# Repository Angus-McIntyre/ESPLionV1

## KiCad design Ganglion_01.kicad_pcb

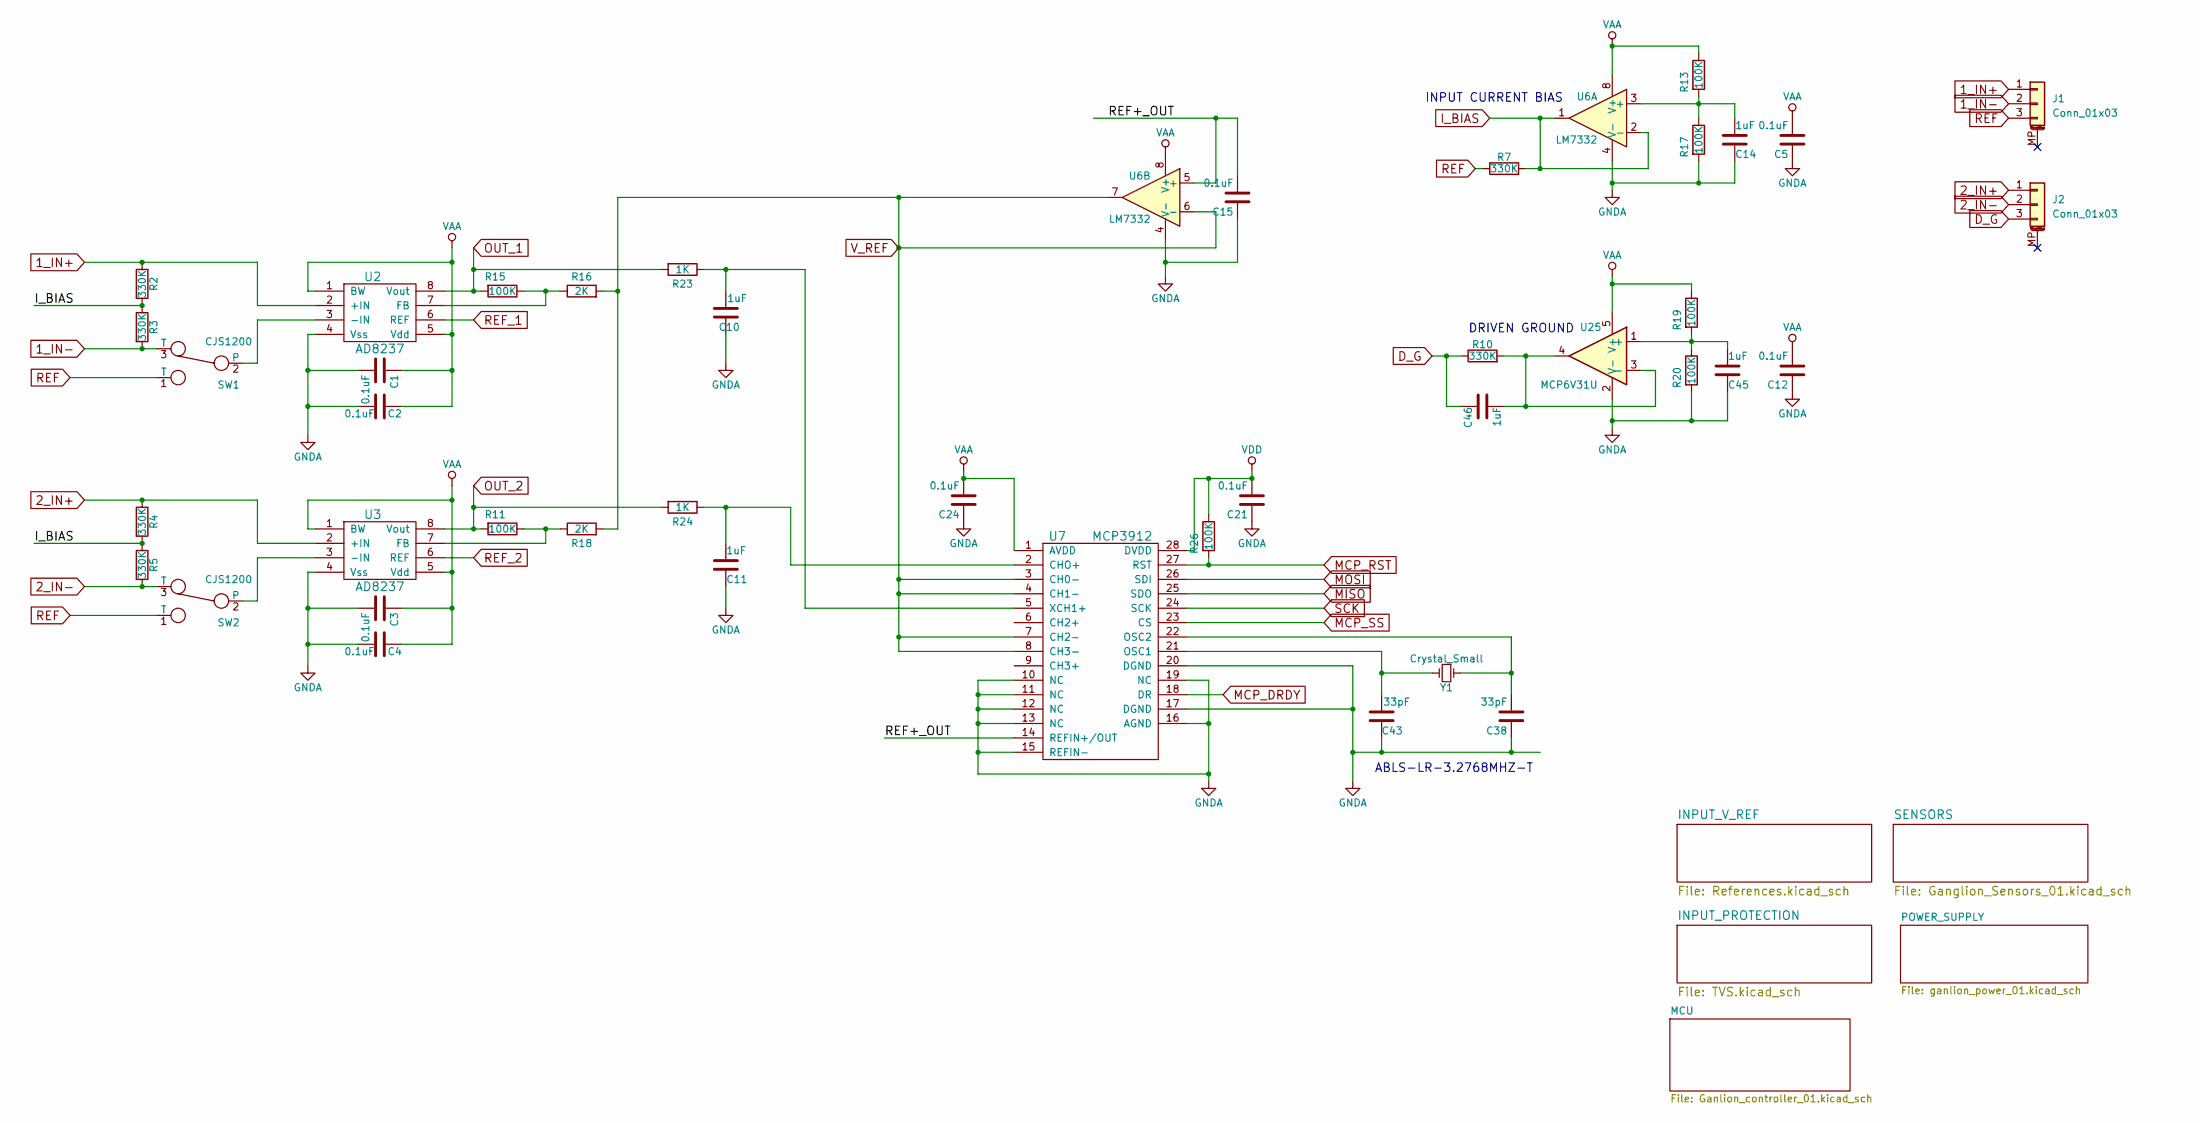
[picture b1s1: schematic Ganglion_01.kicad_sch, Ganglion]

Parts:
C1, C2, C3, C4, C5, C12, C15, C21, C24: 0.1uF; C_0402_1005Metric; MPN GRM155R71C104KA88J
C10, C11, C14, C45, C46: 1uF; C_0603_1608Metric; MPN CC0603KRX7R7BB105
C38, C43: 33pF; C_0603_1608Metric; MPN CL10C330JB8NNNC
J1, J2: Conn_01x03; JST_PH_S3B-PH-SM4-TB_1x03-1MP_P2.00mm_Horizontal; MPN S3B-PH-SM4-TB
R2, R3, R4, R5, R7, R10: 330K; R_0402_1005Metric; MPN ERJ-2RKF3303X
R11, R13, R15, R17, R19, R20, R26: 100K; R_0402_1005Metric; MPN ERJ-2RKF1003X
R16, R18: 2K; R_0402_1005Metric; MPN ERJ-2RKF2001X
R23, R24: 1K; R_0402_1005Metric; MPN ERJ-2RKF1001X
SW1, SW2: CJS1200; CJS-1200TA; MPN CJS-1200TA
U2, U3: AD8237; MSOP-8_3x3mm_P0.65mm; MPN AD8237ARMZ
U6: LM7332; MSOP-8_3x3mm_P0.65mm; MPN LM7332MMX/NOPB
U7: MCP3912; SSOP-28_5.3x10.2mm_P0.65mm; MPN MCP3912A1-E/SS
U25: MCP6V31U; SOT-353_SC-70-5; MPN MCP6V31UT-E/LT
Y1: Crystal_Small; Crystal_SMD_HC49-SD; MPN ABLS-LR-3.2768MHZ-T

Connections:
1_IN+: J1.1, R2.1, U2.2 (+IN); also elsewhere on the board
1_IN-: J1.2, R3.2, SW1.3 (T); also elsewhere on the board
2_IN+: J2.1, R4.1, U3.2 (+IN); also elsewhere on the board
2_IN-: J2.2, R5.2, SW2.3 (T); also elsewhere on the board
/REF+_OUT: C15.2, U6.5 (+), U7.14 (REFIN+/OUT)
D_G: C46.2, J2.3, R10.1; also elsewhere on the board
GNDA: C1.2, C2.2, C3.2, C4.2, C5.1, C10.1, C11.2, C12.1, C14.2, C15.1, C21.1, C24.1, C38.1, C43.1, C45.2, R17.2, R20.2, U2.4 (Vss), U3.4 (Vss), U6.4 (V-), U7.10 (NC), U7.11 (NC), U7.12 (NC), U7.13 (NC), U7.15 (REFIN-), U7.16 (AGND), U7.17 (DGND), U7.19 (NC), U7.20 (DGND), U25.2 (V-); also elsewhere on the board
I_BIAS: R2.2, R3.1, R4.2, R5.1, R7.2, U6.1, U6.2 (-)
MCP_DRDY: U7.18 (DR); also elsewhere on the board
MCP_RST: R26.2, U7.27 (RST); also elsewhere on the board
MCP_SS: U7.23 (CS); also elsewhere on the board
MISO: U7.25 (SDO); also elsewhere on the board
MOSI: U7.26 (SDI); also elsewhere on the board
unnamed: SW1.2, U2.3 (-IN)
unnamed: SW2.2, U3.3 (-IN)
unnamed: R15.1, R16.1, U2.7 (FB)
unnamed: R11.1, R18.1, U3.7 (FB)
unnamed: C14.1, R13.2, R17.1, U6.3 (+)
unnamed: C11.1, R24.1, U7.2 (CHO+)
unnamed: C43.2, U7.21 (OSC1), Y1.2
unnamed: C38.2, U7.22 (OSC2), Y1.1
unnamed: C10.2, R23.1, U7.5 (XCH1+)
unnamed: C45.1, R19.2, R20.1, U25.1 (+)
unnamed: C46.1, R10.2, U25.3 (-), U25.4
OUT_1: R15.2, R23.2, U2.8 (Vout); also elsewhere on the board
OUT_2: R11.2, R24.2, U3.8 (Vout); also elsewhere on the board
REF: J1.3, R7.1, SW1.1 (T), SW2.1 (T); also elsewhere on the board
REF_1: U2.6 (REF); also elsewhere on the board
REF_2: U3.6 (REF); also elsewhere on the board
SCK: U7.24 (SCK); also elsewhere on the board
VAA: C1.1, C2.1, C3.1, C4.1, C5.2, C12.2, C24.2, R13.1, R19.1, U2.1 (BW), U2.5 (Vdd), U3.1 (BW), U3.5 (Vdd), U6.8 (V+), U7.1 (AVDD), U25.5 (V+); also elsewhere on the board
VDD: C21.2, R26.1, U7.28 (DVDD); also elsewhere on the board
V_REF: R16.2, R18.2, U6.6 (-), U6.7, U7.3 (CH0-), U7.4 (CH1-), U7.7 (CH2-), U7.8 (CH3-); also elsewhere on the board

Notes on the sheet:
INPUT CURRENT BIAS
ABLS-LR-3.2768MHZ-T
DRIVEN GROUND

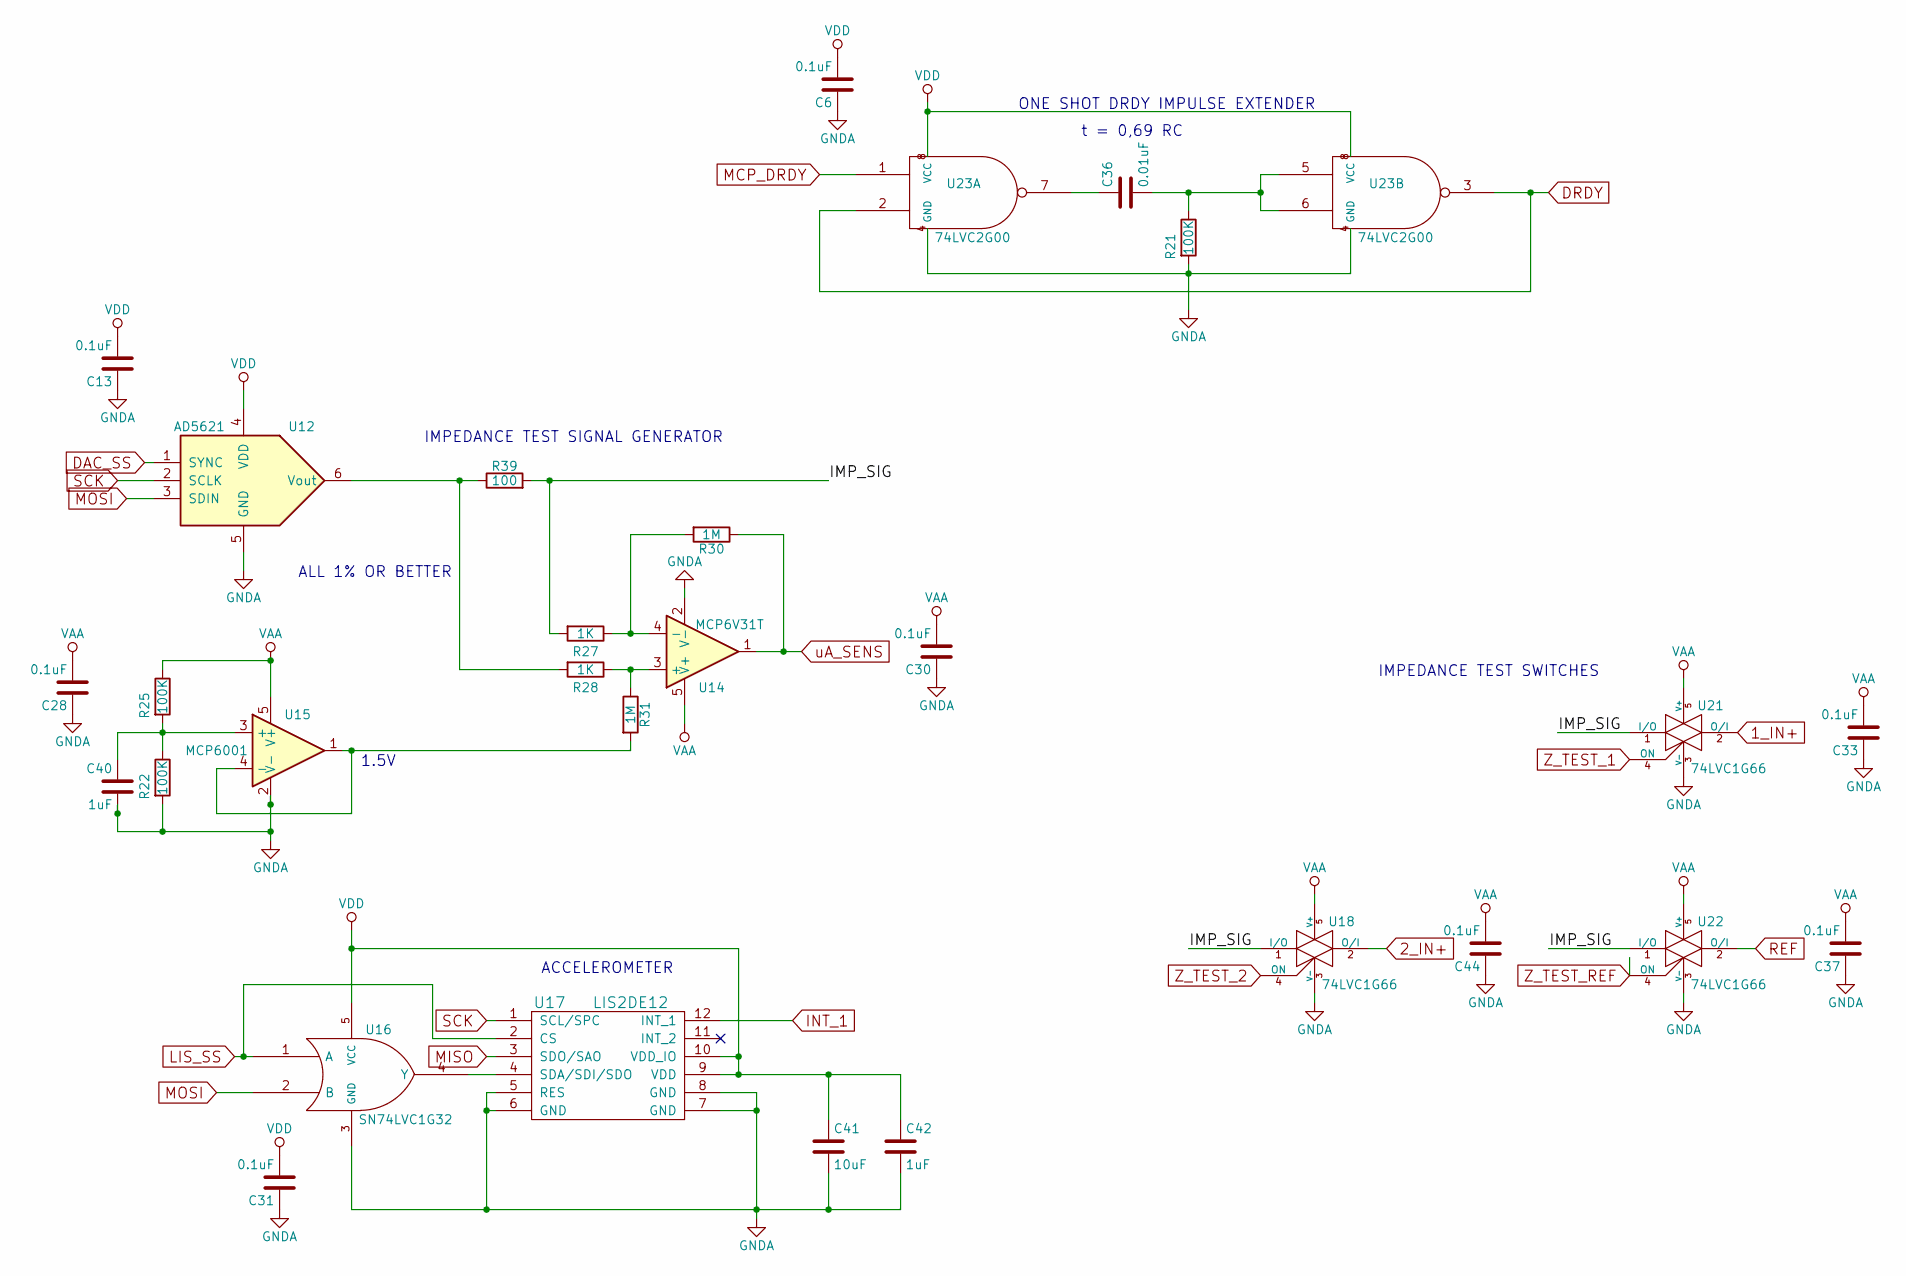
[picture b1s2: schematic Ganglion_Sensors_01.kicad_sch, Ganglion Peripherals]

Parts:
C6, C13, C28, C30, C31, C33, C37, C44: 0.1uF; C_0402_1005Metric; MPN GRM155R71C104KA88J
C36: 0.01uF; C_0603_1608Metric; MPN GCM188R72A103KA37D
C40, C42: 1uF; C_0603_1608Metric; MPN CC0603KRX7R7BB105
C41: 10uF; C_0603_1608Metric; MPN GRM188R60J106KE47D
R21, R22, R25: 100K; R_0402_1005Metric; MPN ERJ-2RKF1003X
R27, R28: 1K; R_0402_1005Metric; MPN ERJ-2RKF1001X
R30, R31: 1M; R_0402_1005Metric; MPN ERJ-2RKF1004X
R39: 100; R_0603_1608Metric; MPN ERA-3AEB101V
U12: AD5621; SOT-363_SC-70-6; MPN AD5621AKSZ-REEL7
U14: MCP6V31T; SOT-23-5; MPN MCP6V31T-E/OT
U15: MCP6001; SOT-353_SC-70-5; MPN MCP6001T-I/LT
U16: SN74LVC1G32; SOT-353_SC-70-5; MPN SN74LVC1G32DCKR
U17: LIS2DE12; LIS2DH12; MPN LIS2DE12TR
U18, U21, U22: 74LVC1G66; SOT-353_SC-70-5; MPN 74LVC1G66GW,125
U23: 74LVC2G00; VSSOP-8; MPN SN74LVC2G00DCUR

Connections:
1_IN+: U21.2 (O/I); also elsewhere on the board
2_IN+: U18.2 (O/I); also elsewhere on the board
/SENSORS/IMP_SIG: R27.2, R39.2, U18.1 (I/O), U21.1 (I/O), U22.1 (I/O)
DAC_SS: U12.1 (SYNC); also elsewhere on the board
DRDY: U23.2, U23.3; also elsewhere on the board
GNDA: C6.1, C13.1, C28.1, C30.1, C31.1, C33.1, C37.1, C40.2, C41.2, C42.2, C44.1, R21.2, R22.2, U12.5 (GND), U14.2 (V-), U15.2 (V-), U16.3 (GND), U17.5 (RES), U17.6 (GND), U17.7 (GND), U17.8 (GND), U18.3 (V-), U21.3 (V-), U22.3 (V-), U23.4 (GND); also elsewhere on the board
INT_1: U17.12 (INT_1); also elsewhere on the board
LIS_SS: U16.1 (A), U17.2 (CS); also elsewhere on the board
MCP_DRDY: U23.1; also elsewhere on the board
MISO: U17.3 (SDO/SAO); also elsewhere on the board
MOSI: U12.3 (SDIN), U16.2 (B); also elsewhere on the board
unnamed: C36.1, U23.7
unnamed: C36.2, R21.1, U23.5, U23.6
unnamed: R28.2, R39.1, U12.6 (Vout)
unnamed: R28.1, R31.1, U14.3 (+)
unnamed: R27.1, R30.2, U14.4 (-)
unnamed: C40.1, R22.1, R25.2, U15.3 (+)
unnamed: R31.2, U15.1, U15.4 (-)
unnamed: U16.4 (Y), U17.4 (SDA/SDI/SDO)
REF: U22.2 (O/I); also elsewhere on the board
SCK: U12.2 (SCLK), U17.1 (SCL/SPC); also elsewhere on the board
VAA: C28.2, C30.2, C33.2, C37.2, C44.2, R25.1, U14.5 (V+), U15.5 (V+), U18.5 (V+), U21.5 (V+), U22.5 (V+); also elsewhere on the board
VDD: C6.2, C13.2, C31.2, C41.1, C42.1, U12.4 (VDD), U16.5 (VCC), U17.9 (VDD), U17.10 (VDD_IO), U23.8 (VCC); also elsewhere on the board
Z_TEST_1: U21.4 (ON); also elsewhere on the board
Z_TEST_2: U18.4 (ON); also elsewhere on the board
Z_TEST_REF: U22.4 (ON); also elsewhere on the board
uA_SENS: R30.1, U14.1; also elsewhere on the board

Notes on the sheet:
ONE SHOT DRDY IMPULSE EXTENDER
t = 0,69 RC
1.5V
ACCELEROMETER
IMPEDANCE TEST SIGNAL GENERATOR
ALL 1% OR BETTER
IMPEDANCE TEST SWITCHES

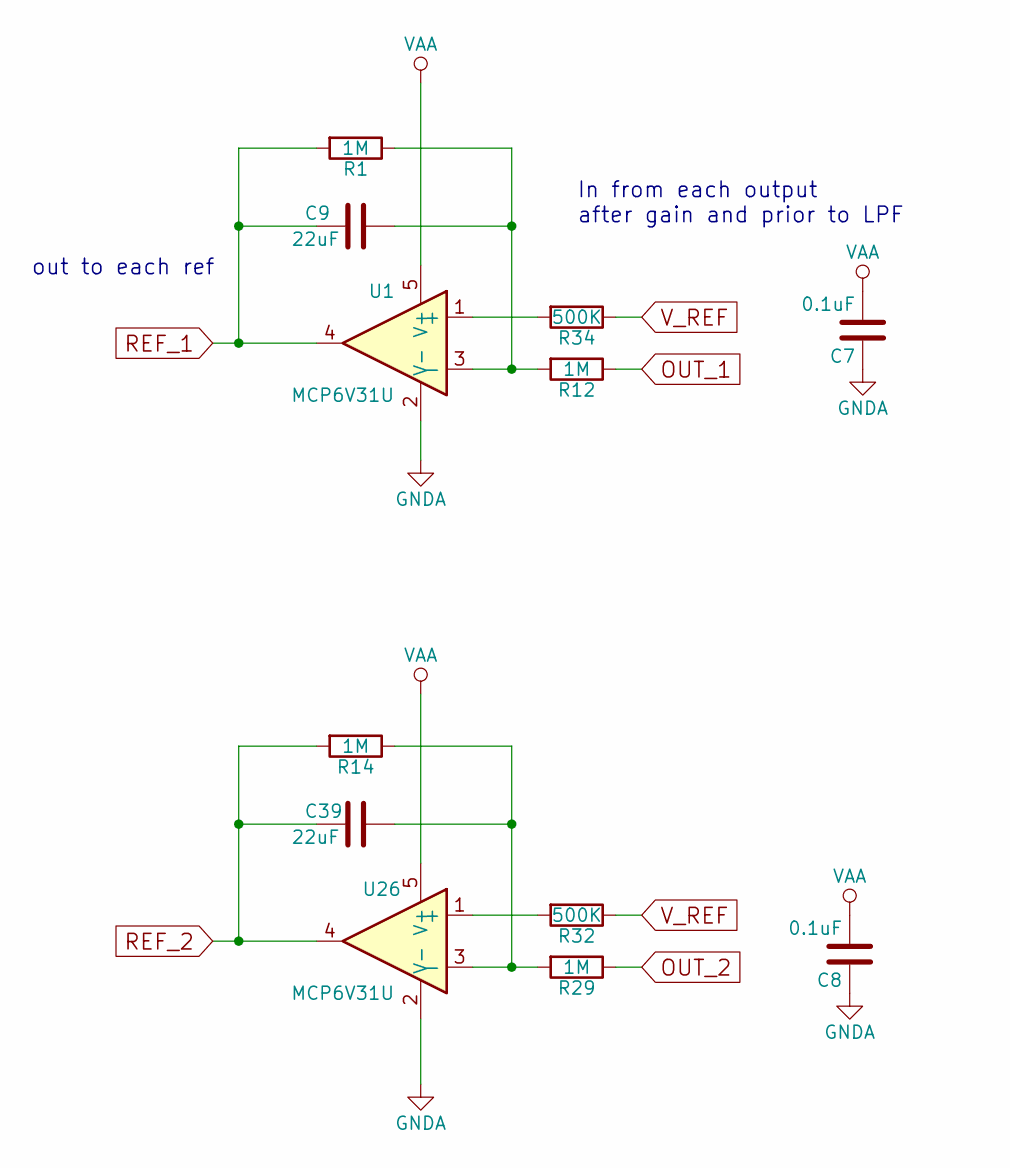
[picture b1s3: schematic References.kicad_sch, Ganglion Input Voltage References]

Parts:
C7, C8: 0.1uF; C_0402_1005Metric; MPN GRM155R71C104KA88J
C9, C39: 22uF; C_0603_1608Metric; MPN GRM188R60J226MEA0D
R1, R12, R14, R29: 1M; R_0402_1005Metric; MPN ERJ-2RKF1004X
R32, R34: 500K; R_0402_1005Metric; MPN ERJ-2RKF4993X
U1, U26: MCP6V31U; SOT-353_SC-70-5; MPN MCP6V31UT-E/LT

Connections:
GNDA: C7.1, C8.1, U1.2 (V-), U26.2 (V-); also elsewhere on the board
unnamed: R34.2, U1.1 (+)
unnamed: C9.1, R1.1, R12.2, U1.3 (-)
unnamed: R32.2, U26.1 (+)
unnamed: C39.1, R14.1, R29.2, U26.3 (-)
OUT_1: R12.1; also elsewhere on the board
OUT_2: R29.1; also elsewhere on the board
REF_1: C9.2, R1.2, U1.4; also elsewhere on the board
REF_2: C39.2, R14.2, U26.4; also elsewhere on the board
VAA: C7.2, C8.2, U1.5 (V+), U26.5 (V+); also elsewhere on the board
V_REF: R32.1, R34.1; also elsewhere on the board

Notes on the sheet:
In from each output after gain and prior to LPF
out to each ref

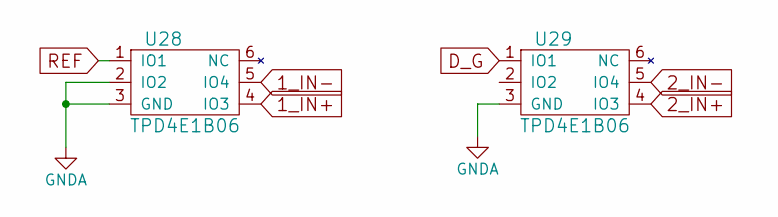
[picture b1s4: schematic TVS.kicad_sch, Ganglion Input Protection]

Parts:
U28, U29: TPD4E1B06; SOT-363_SC-70-6; MPN TPD4E1B06DCKR

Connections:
1_IN+: U28.4 (IO3); also elsewhere on the board
1_IN-: U28.5 (IO4); also elsewhere on the board
2_IN+: U29.4 (IO3); also elsewhere on the board
2_IN-: U29.5 (IO4); also elsewhere on the board
D_G: U29.1 (IO1); also elsewhere on the board
GNDA: U28.2 (IO2), U28.3 (GND), U29.3 (GND); also elsewhere on the board
REF: U28.1 (IO1); also elsewhere on the board

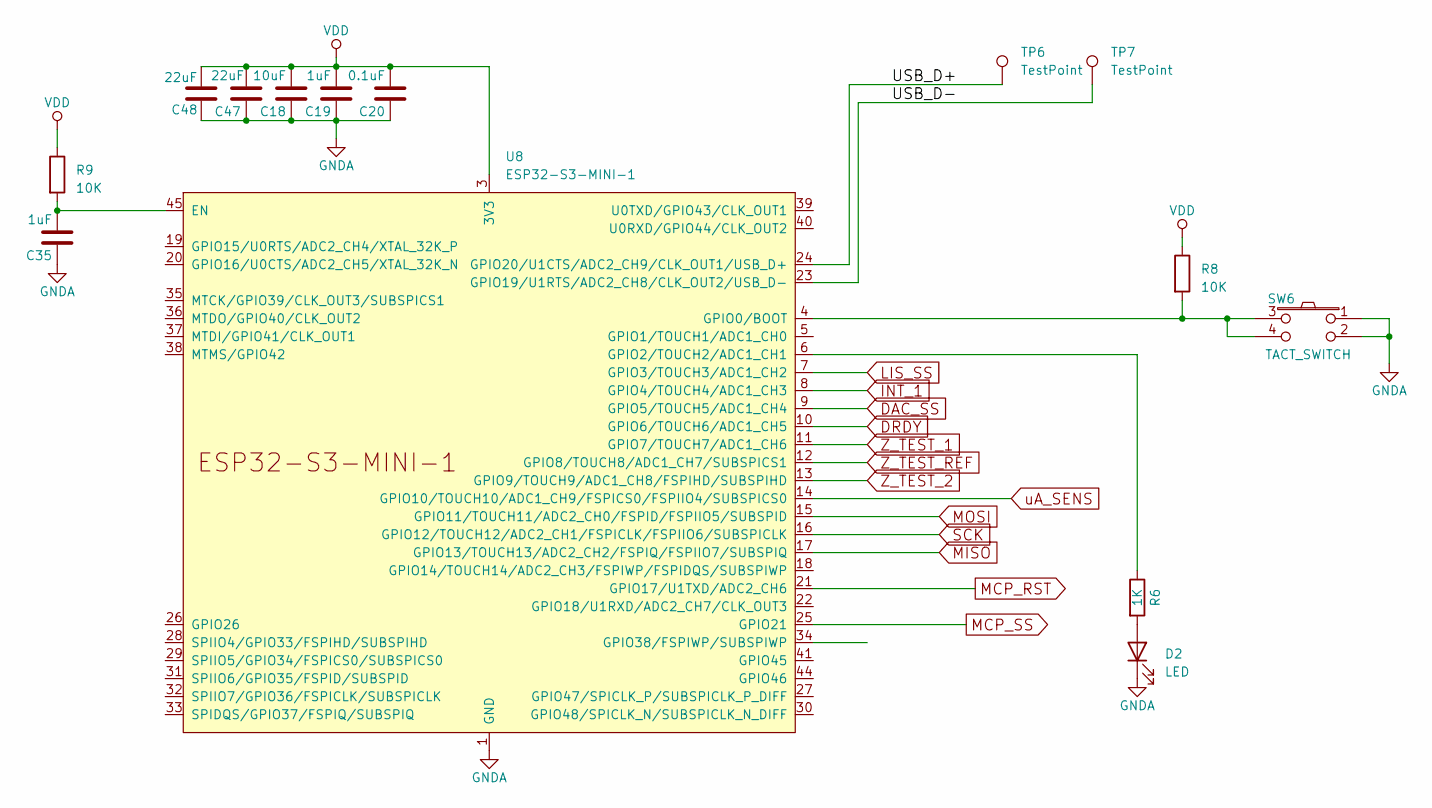
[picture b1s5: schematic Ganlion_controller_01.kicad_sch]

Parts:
C18: 10uF; C_0603_1608Metric; MPN GRM188R60J106KE47D
C19, C35: 1uF; C_0603_1608Metric; MPN CC0603KRX7R7BB105
C20: 0.1uF; C_0402_1005Metric; MPN GRM155R71C104KA88J
C47, C48: 22uF; C_0603_1608Metric; MPN GRM188R60J226MEA0D
D2: LED; LED_0603_1608Metric_Pad1.05x0.95mm_HandSolder; MPN 150060VS75003
R6: 1K; R_0402_1005Metric; MPN ERJ-2RKF1001X
R8, R9: 10K; R_0402_1005Metric; MPN ERJ-2RKF1002X
SW6: TACT_SWITCH; PTS810; MPN PTS810 SJK 250 SMTR LFS
TP6, TP7: TestPoint; TestPoint_Pad_D1.5mm
U8: ESP32-S3-MINI-1; MPN ESP32-S3-MINI-1-N8

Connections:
/MCU/USB_D+: TP6.1, U8.24 (GPIO20/U1CTS/ADC2_CH9/CLK_OUT1/USB_D+)
/MCU/USB_D-: TP7.1, U8.23 (GPIO19/U1RTS/ADC2_CH8/CLK_OUT2/USB_D-)
DAC_SS: U8.9 (GPIO5/TOUCH5/ADC1_CH4); also elsewhere on the board
DRDY: U8.10 (GPIO6/TOUCH6/ADC1_CH5); also elsewhere on the board
GNDA: C18.1, C19.1, C20.1, C35.1, C47.2, C48.2, D2.1 (K), SW6.1, SW6.2, U8.1 (GND), U8.2 (GND), U8.42 (GND), U8.43 (GND), U8.46 (GND), U8.47 (GND), U8.48 (GND), U8.49 (GND), U8.50 (GND), U8.51 (GND), U8.52 (GND), U8.53 (GND), U8.54 (GND), U8.55 (GND), U8.56 (GND), U8.57 (GND), U8.58 (GND), U8.59 (GND), U8.60 (GND), U8.61 (GND), U8.62 (GND), U8.63 (GND), U8.64 (GND), U8.65 (GND); also elsewhere on the board
INT_1: U8.8 (GPIO4/TOUCH4/ADC1_CH3); also elsewhere on the board
LIS_SS: U8.7 (GPIO3/TOUCH3/ADC1_CH2); also elsewhere on the board
MCP_RST: U8.21 (GPIO17/U1TXD/ADC2_CH6); also elsewhere on the board
MCP_SS: U8.25 (GPIO21); also elsewhere on the board
MISO: U8.17 (GPIO13/TOUCH13/ADC2_CH2/FSPIQ/FSPIIO7/S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); also elsewhere on the board
MOSI: U8.15 (GPIO11/TOUCH11/ADC2_CH0/FSPID/FSPIIO5/S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); also elsewhere on the board
unnamed: D2.2 (A), R6.2
unnamed: C35.2, R9.2, U8.45 (EN)
unnamed: R8.2, SW6.3, SW6.4, U8.4 (GPIO0/BOOT)
unnamed: R6.1, U8.6 (GPIO2/TOUCH2/ADC1_CH1)
SCK: U8.16 (GPIO12/TOUCH12/ADC2_CH1/FSPICLK/FSPIIO6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); also elsewhere on the board
VDD: C18.2, C19.2, C20.2, C47.1, C48.1, R8.1, R9.1, U8.3 (3V3); also elsewhere on the board
Z_TEST_1: U8.11 (GPIO7/TOUCH7/ADC1_CH6); also elsewhere on the board
Z_TEST_2: U8.13 (GPIO9/TOUCH9/ADC1_CH8/FSPIHD/SUBSPIHD); also elsewhere on the board
Z_TEST_REF: U8.12 (GPIO8/TOUCH8/ADC1_CH7/SUBSPICS1); also elsewhere on the board
uA_SENS: U8.14 (GPIO10/TOUCH10/ADC1_CH9/FSPICS0/FSPIIO4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); also elsewhere on the board

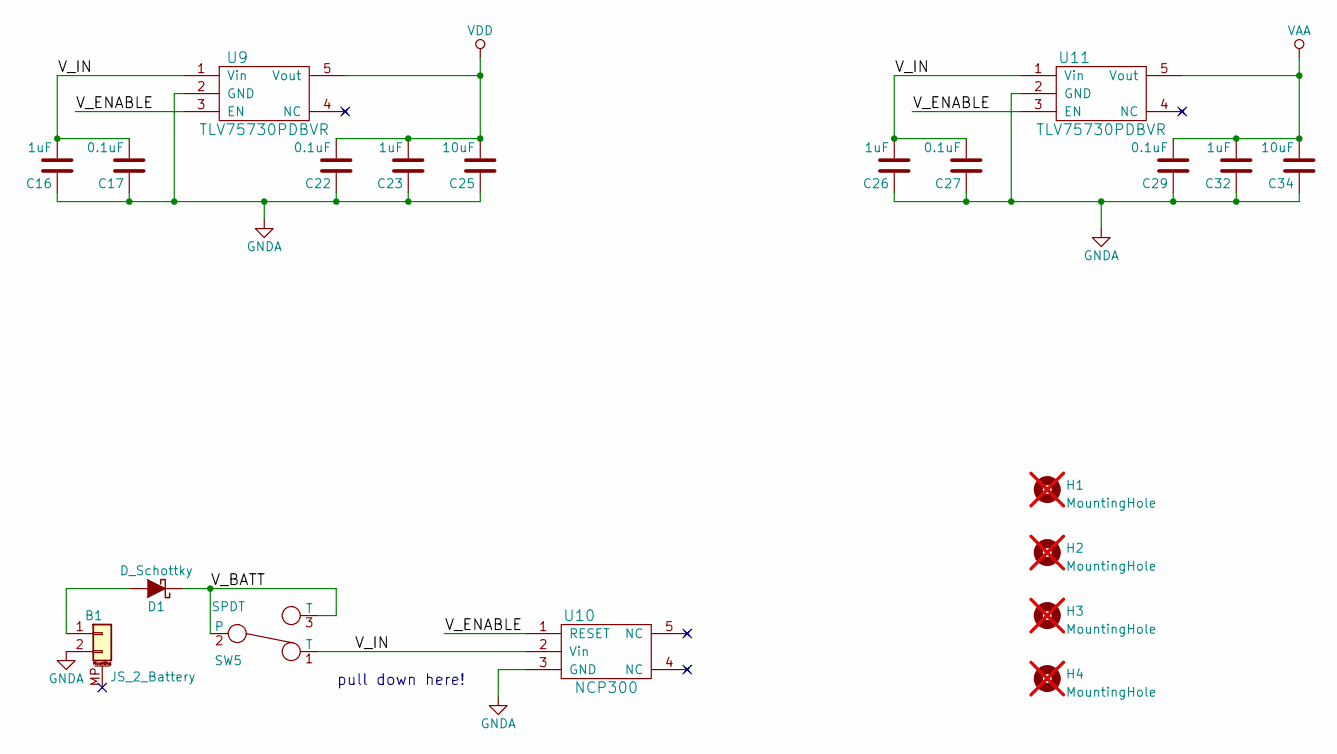
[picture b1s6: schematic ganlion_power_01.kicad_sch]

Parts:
B1: JS_2_Battery; JST_PH_S2B-PH-SM4-TB_1x02-1MP_P2.00mm_Horizontal; MPN S2B-PH-SM4-TB
C16, C23, C26, C32: 1uF; C_0603_1608Metric; MPN CC0603KRX7R7BB105
C17, C22, C27, C29: 0.1uF; C_0402_1005Metric; MPN GRM155R71C104KA88J
C25, C34: 10uF; C_0603_1608Metric; MPN GRM188R60J106KE47D
D1: D_Schottky; C_0603_1608Metric; MPN CDBU0130L
H1, H2, H3, H4: MountingHole; MountingHole_3.2mm_M3_Pad; not fitted
SW5: SPDT; SSSS810701_SSSS810701; MPN SSSS810701
U9, U11: TLV75730PDBVR; SOT-23-5; MPN TLV75730PDBVR
U10: NCP300; SOT-23-5; MPN BD4930G-TR

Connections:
/POWER_SUPPLY/V_BATT: D1.1 (K), SW5.2, SW5.3 (T)
/POWER_SUPPLY/V_ENABLE: U9.3 (EN), U10.1 (RESET), U11.3 (EN)
/POWER_SUPPLY/V_IN: C16.2, C17.2, C26.2, C27.2, SW5.1 (T), U9.1 (Vin), U10.2 (Vin), U11.1 (Vin)
GNDA: B1.2, C16.1, C17.1, C22.1, C23.1, C25.1, C26.1, C27.1, C29.1, C32.1, C34.1, U9.2 (GND), U10.3 (GND), U11.2 (GND); also elsewhere on the board
unnamed: B1.1, D1.2 (A)
VAA: C29.2, C32.2, C34.2, U11.5 (Vout); also elsewhere on the board
VDD: C22.2, C23.2, C25.2, U9.5 (Vout); also elsewhere on the board

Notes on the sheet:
pull down here!

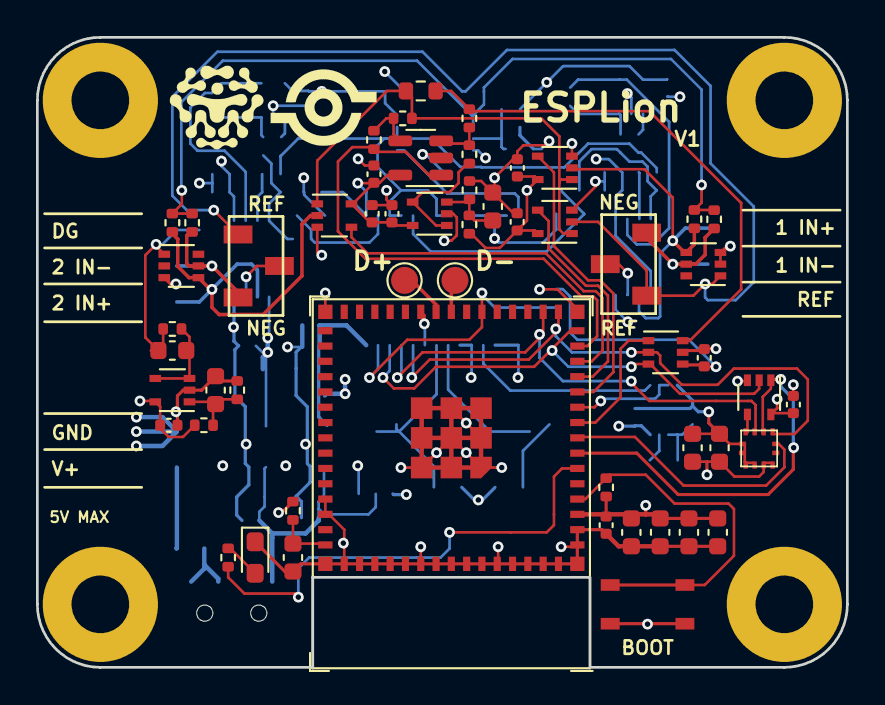
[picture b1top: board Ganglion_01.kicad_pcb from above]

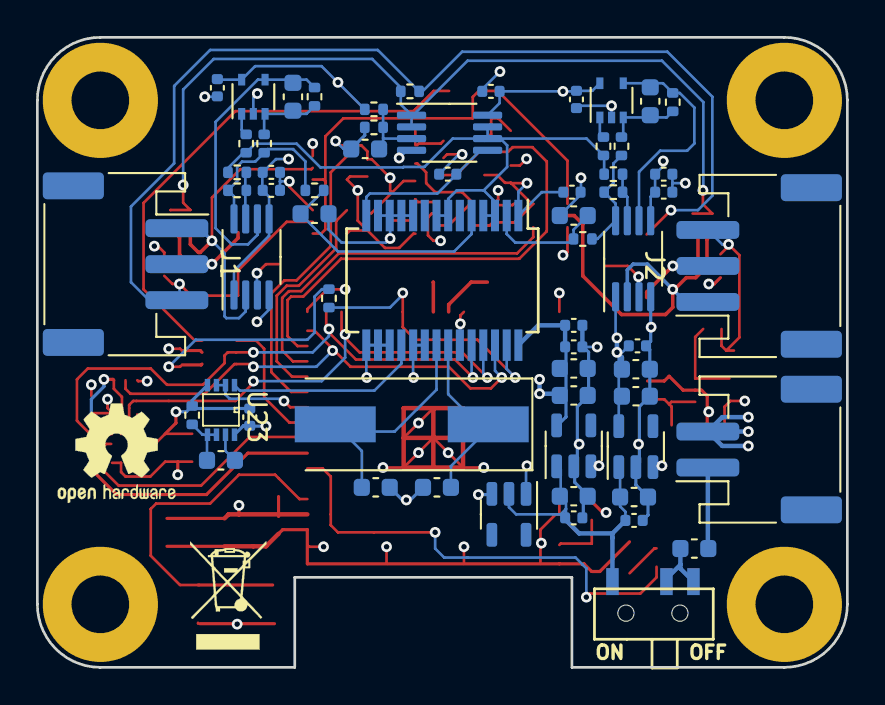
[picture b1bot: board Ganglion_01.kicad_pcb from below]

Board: 4 copper layers, 45.0 x 35.0 mm, 120 parts (62 on the bottom side), 64 nets.

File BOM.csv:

"Reference","Qty","SPN","MPN","Value","Footprint"
"B1","1","455-S2B-PH-SM4-TBCT-ND","S2B-PH-SM4-TB","JS_2_Battery","Connector_JST:JST_PH_S2B-PH-SM4-TB_1x02-1MP_P2.00mm_Horizontal"
"C1 C2 C3 C4 C5 C6 C7 C8 C12 C13 C15 C17 C20 C21 C22 C24 C27 C28 C29 C30 C31 C33 C37 C44","24","490-6328-1-ND","GRM155R71C104KA88J","0.1uF","Capacitor_SMD:C_0402_1005Metric"
"C9 C39 C47 C48","4","490-7611-1-ND","GRM188R60J226MEA0D","22uF","Capacitor_SMD:C_0603_1608Metric"
"C10 C11 C14 C16 C19 C23 C26 C32 C35 C40 C42 C45 C46","13","311-1446-1-ND","CC0603KRX7R7BB105","1uF","Capacitor_SMD:C_0603_1608Metric"
"C18 C25 C34 C41","4","490-12538-1-ND","GRM188R60J106KE47D","10uF","Capacitor_SMD:C_0603_1608Metric"
"C36","1","490-4781-1-ND","GCM188R72A103KA37D","0.01uF","Capacitor_SMD:C_0603_1608Metric"
"C38 C43","2","1276-1070-1-ND","CL10C330JB8NNNC","33pF","Capacitor_SMD:C_0603_1608Metric"
"D1","1","641-1282-1-ND","CDBU0130L","D_Schottky","Capacitor_SMD:C_0603_1608Metric"
"D2","1","710-150060VS75003","150060VS75003","LED","LED_SMD:LED_0603_1608Metric_Pad1.05x0.95mm_HandSolder"
"J1 J2","2","455-S3B-PH-SM4-TBCT-ND","S3B-PH-SM4-TB","Conn_01x03","Connector_JST:JST_PH_S3B-PH-SM4-TB_1x03-1MP_P2.00mm_Horizontal"
"R1 R12 R14 R29 R30 R31","6","P1.00MLCT-ND","ERJ-2RKF1004X","1M","Resistor_SMD:R_0402_1005Metric"
"R2 R3 R4 R5 R7 R10","6","P330KLCT-ND","ERJ-2RKF3303X","330K","Resistor_SMD:R_0402_1005Metric"
"R6 R23 R24 R27 R28","5","P1.00KLCT-ND","ERJ-2RKF1001X","1K","Resistor_SMD:R_0402_1005Metric"
"R8 R9","2","P10.0KLCT-ND","ERJ-2RKF1002X","10K","Resistor_SMD:R_0402_1005Metric"
"R11 R13 R15 R17 R19 R20 R21 R22 R25 R26","10","P100KLCT-ND","ERJ-2RKF1003X","100K","Resistor_SMD:R_0402_1005Metric"
"R16 R18","2","P2.00KLCT-ND","ERJ-2RKF2001X","2K","Resistor_SMD:R_0402_1005Metric"
"R32 R34","2","P499KLCT-ND","ERJ-2RKF4993X","500K","Resistor_SMD:R_0402_1005Metric"
"R39","1","P100DBCT-ND","ERA-3AEB101V","100","Resistor_SMD:R_0603_1608Metric"
"SW1 SW2","2","563-1021-1-ND","CJS-1200TA","CJS1200","OpenBCI_KiCad_library_files:CJS-1200TA"
"SW5","1","4809-SSSS810701CT-ND","SSSS810701","SPDT","OpenBCI_KiCad_library_files:SSSS810701_SSSS810701"
"SW6","1","CKN10503CT-ND","PTS810 SJK 250 SMTR LFS","TACT_SWITCH","OpenBCI_KiCad_library_files:PTS810"
"U1 U25 U26","3","MCP6V31UT-E/LTCT-ND","MCP6V31UT-E/LT","MCP6V31U","Package_TO_SOT_SMD:SOT-353_SC-70-5"
"U2 U3","2","505-AD8237ARMZ-ND","AD8237ARMZ","AD8237","Package_SO:MSOP-8_3x3mm_P0.65mm"
"U6","1","296-LM7332MMX/NOPBCT-ND","LM7332MMX/NOPB","LM7332","Package_SO:MSOP-8_3x3mm_P0.65mm"
"U7","1","579-MCP3912A1-E/SS","MCP3912A1-E/SS","MCP3912","Package_SO:SSOP-28_5.3x10.2mm_P0.65mm"
"U8","1","1965-ESP32-S3-MINI-1-N8CT-ND","ESP32-S3-MINI-1-N8","ESP32-S3-MINI-1","Espressif:ESP32-S3-MINI-1"
"U9 U11","2","296-51819-1-ND","TLV75730PDBVR","TLV75730PDBVR","Package_TO_SOT_SMD:SOT-23-5"
"U10","1","BD4930GCT-ND","BD4930G-TR","NCP300","Package_TO_SOT_SMD:SOT-23-5"
"U12","1","AD5621AKSZ-REEL7CT-ND","AD5621AKSZ-REEL7","AD5621","Package_TO_SOT_SMD:SOT-363_SC-70-6"
"U14","1","MCP6V31T-E/OTCT-ND","MCP6V31T-E/OT","MCP6V31T","Package_TO_SOT_SMD:SOT-23-5"
"U15","1","MCP6001T-I/LTCT-ND","MCP6001T-I/LT","MCP6001","Package_TO_SOT_SMD:SOT-353_SC-70-5"
"U16","1","296-9848-1-ND","SN74LVC1G32DCKR","SN74LVC1G32","Package_TO_SOT_SMD:SOT-353_SC-70-5"
"U17","1","497-15997-1-ND","LIS2DE12TR","LIS2DE12","OpenBCI_KiCad_library_files:LIS2DH12"
"U18 U21 U22","3","1727-4118-1-ND","74LVC1G66GW,125","74LVC1G66","Package_TO_SOT_SMD:SOT-353_SC-70-5"
"U23","1","296-13258-1-ND","SN74LVC2G00DCUR","74LVC2G00","OpenBCI_KiCad_library_files:VSSOP-8"
"U28 U29","2","296-39346-1-ND","TPD4E1B06DCKR","TPD4E1B06","Package_TO_SOT_SMD:SOT-363_SC-70-6"
"Y1","1","535-10160-1-ND","ABLS-LR-3.2768MHZ-T","Crystal_Small","Crystal:Crystal_SMD_HC49-SD"

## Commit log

2025-06-01 Add 3d model
2025-06-01 Rename project
2025-06-01 Clean up
2025-06-01 Release files
2025-06-01 BOM cleanup
2025-06-01 Add license file
